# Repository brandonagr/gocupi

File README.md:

Create Thick TSP
================
forked the code in order to draw thicker lines to get more contrast. For detailed descriptions see file createThickTSP
How to set start point and pinup see http://4um.gocupi.com/t/draw-tsp-with-different-line-thickness/61

gocupi
======

Polargraph (vertical plotter / drawing machine) written in Go. Inspired by [Polargraph](http://www.polargraph.co.uk/) and [drawbot](http://marginallyclever.com/blog/drawbot/) projects, designed with the help of the [Dallas Makerspace](http://dallasmakerspace.org/)

Gocupi is different from existing systems in that it uses a Raspberry Pi to do most of the processing instead of relying on a microcontroller to parse commands. This gives it the ability to render complex svg files and patterns that would not fit in memory on a microcontroller.

**A kit with all the hardware needed is now [available at gocupi.com](http://www.gocupi.com/store/)**

Check out the [project page](http://brandonagr.github.io/gocupi/) for a general description, there are also several [wiki pages](https://github.com/brandonagr/gocupi/wiki) with additional information as well as a [forum](http://4um.gocupi.com).

Custom Linux Distro
===================

You can now [download](https://www.dropbox.com/s/6l89m04kcqiwlgb/gocupi_boot_image.zip?dl=0) a custom linux distrobution built from Raspbian with all gocupi software pre-installed.
Unzip the download and copy files to blank SD card (do not build the image). Put the card in the Pi and Bob's your uncle.

If you choose the method above (custom linux distro) then you can skip to the bottom of this document to section "Run gocupi".

Manual Installation Quickstart Guide
================

(Start with something well supported i.e. Raspbian Wheezy.) 

Install Go
-----------
The full install guide is on [golang.org](http://golang.org/doc/install). For the Raspberry Pi you can [download precompiled binaries](http://dave.cheney.net/unofficial-arm-tarballs) to avoid the lengthy process of building go from source.

For example, installing go to the default location with a precompiled binary on a raspberry pi just takes 3 commands:

    wget http://dave.cheney.net/paste/go.1.3.linux-arm~multiarch-armv6-1.tar.gz
    sudo tar -C /usr/local -xzf go.1.3.linux-arm~multiarch-armv6-1.tar.gz
    sudo echo 'export PATH=$PATH:/usr/local/go/bin' >> ~/.profile

(You must set GOROOT also if you install go to someplace besides the default /usr/local/go)

Fix the serial communication (for Raspberry Pi)
----------------------------
Change the default serial communication by editing /boot/cmdline.txt and remove references to `/dev/ttyAMA0`

Disable the getty on that serial port in /etc/inittab by commenting out references to `/dev/ttyAMA0`

In order to reset the serial communication port we need to `sudo reboot`

Setup gopath folder
----------------------------
Setup the folder for your gopath and set some path variables

    mkdir ~/gopath
    sudo echo 'export GOPATH=$HOME/gopath' >> ~/.profile
    sudo echo 'export PATH=$PATH:$HOME/gopath/bin' >> ~/.profile

Install needed dependency
---------------------
Update apt-get, install mercurial, and reboot

    sudo apt-get update
    sudo apt-get install mercurial
    sudo reboot

Download and build gocupi
---------------------------
From your home directory

    go get github.com/brandonagr/gocupi

Run gocupi
----------
`gocupi` The gocupi executable should now be in your $GOPATH\bin folder, you can run the command with no arguments to display the help and what command are available

`gocupi setup 1000 700 700` The setup command can be used to initialize the dimensions of the polargraph hardware, the setup is stored in the generated gocupi_config.xml file

`gocupi -toimage grid 100 10` The -toimage flag causes the system to draw to an output.png instead of trying to control the stepper motors over serial

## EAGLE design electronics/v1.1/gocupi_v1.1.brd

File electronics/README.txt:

Designs are a work in progress, issues may be submitted through the repository at https://github.com/brandonagr/gocupi or emailed directly to Brandon Dunson 'dunson at gocupi dot com'

gocupi hardware by Brandon Dunson is licensed under a Creative Commons Attribution-SharAlike 4.0 International License.

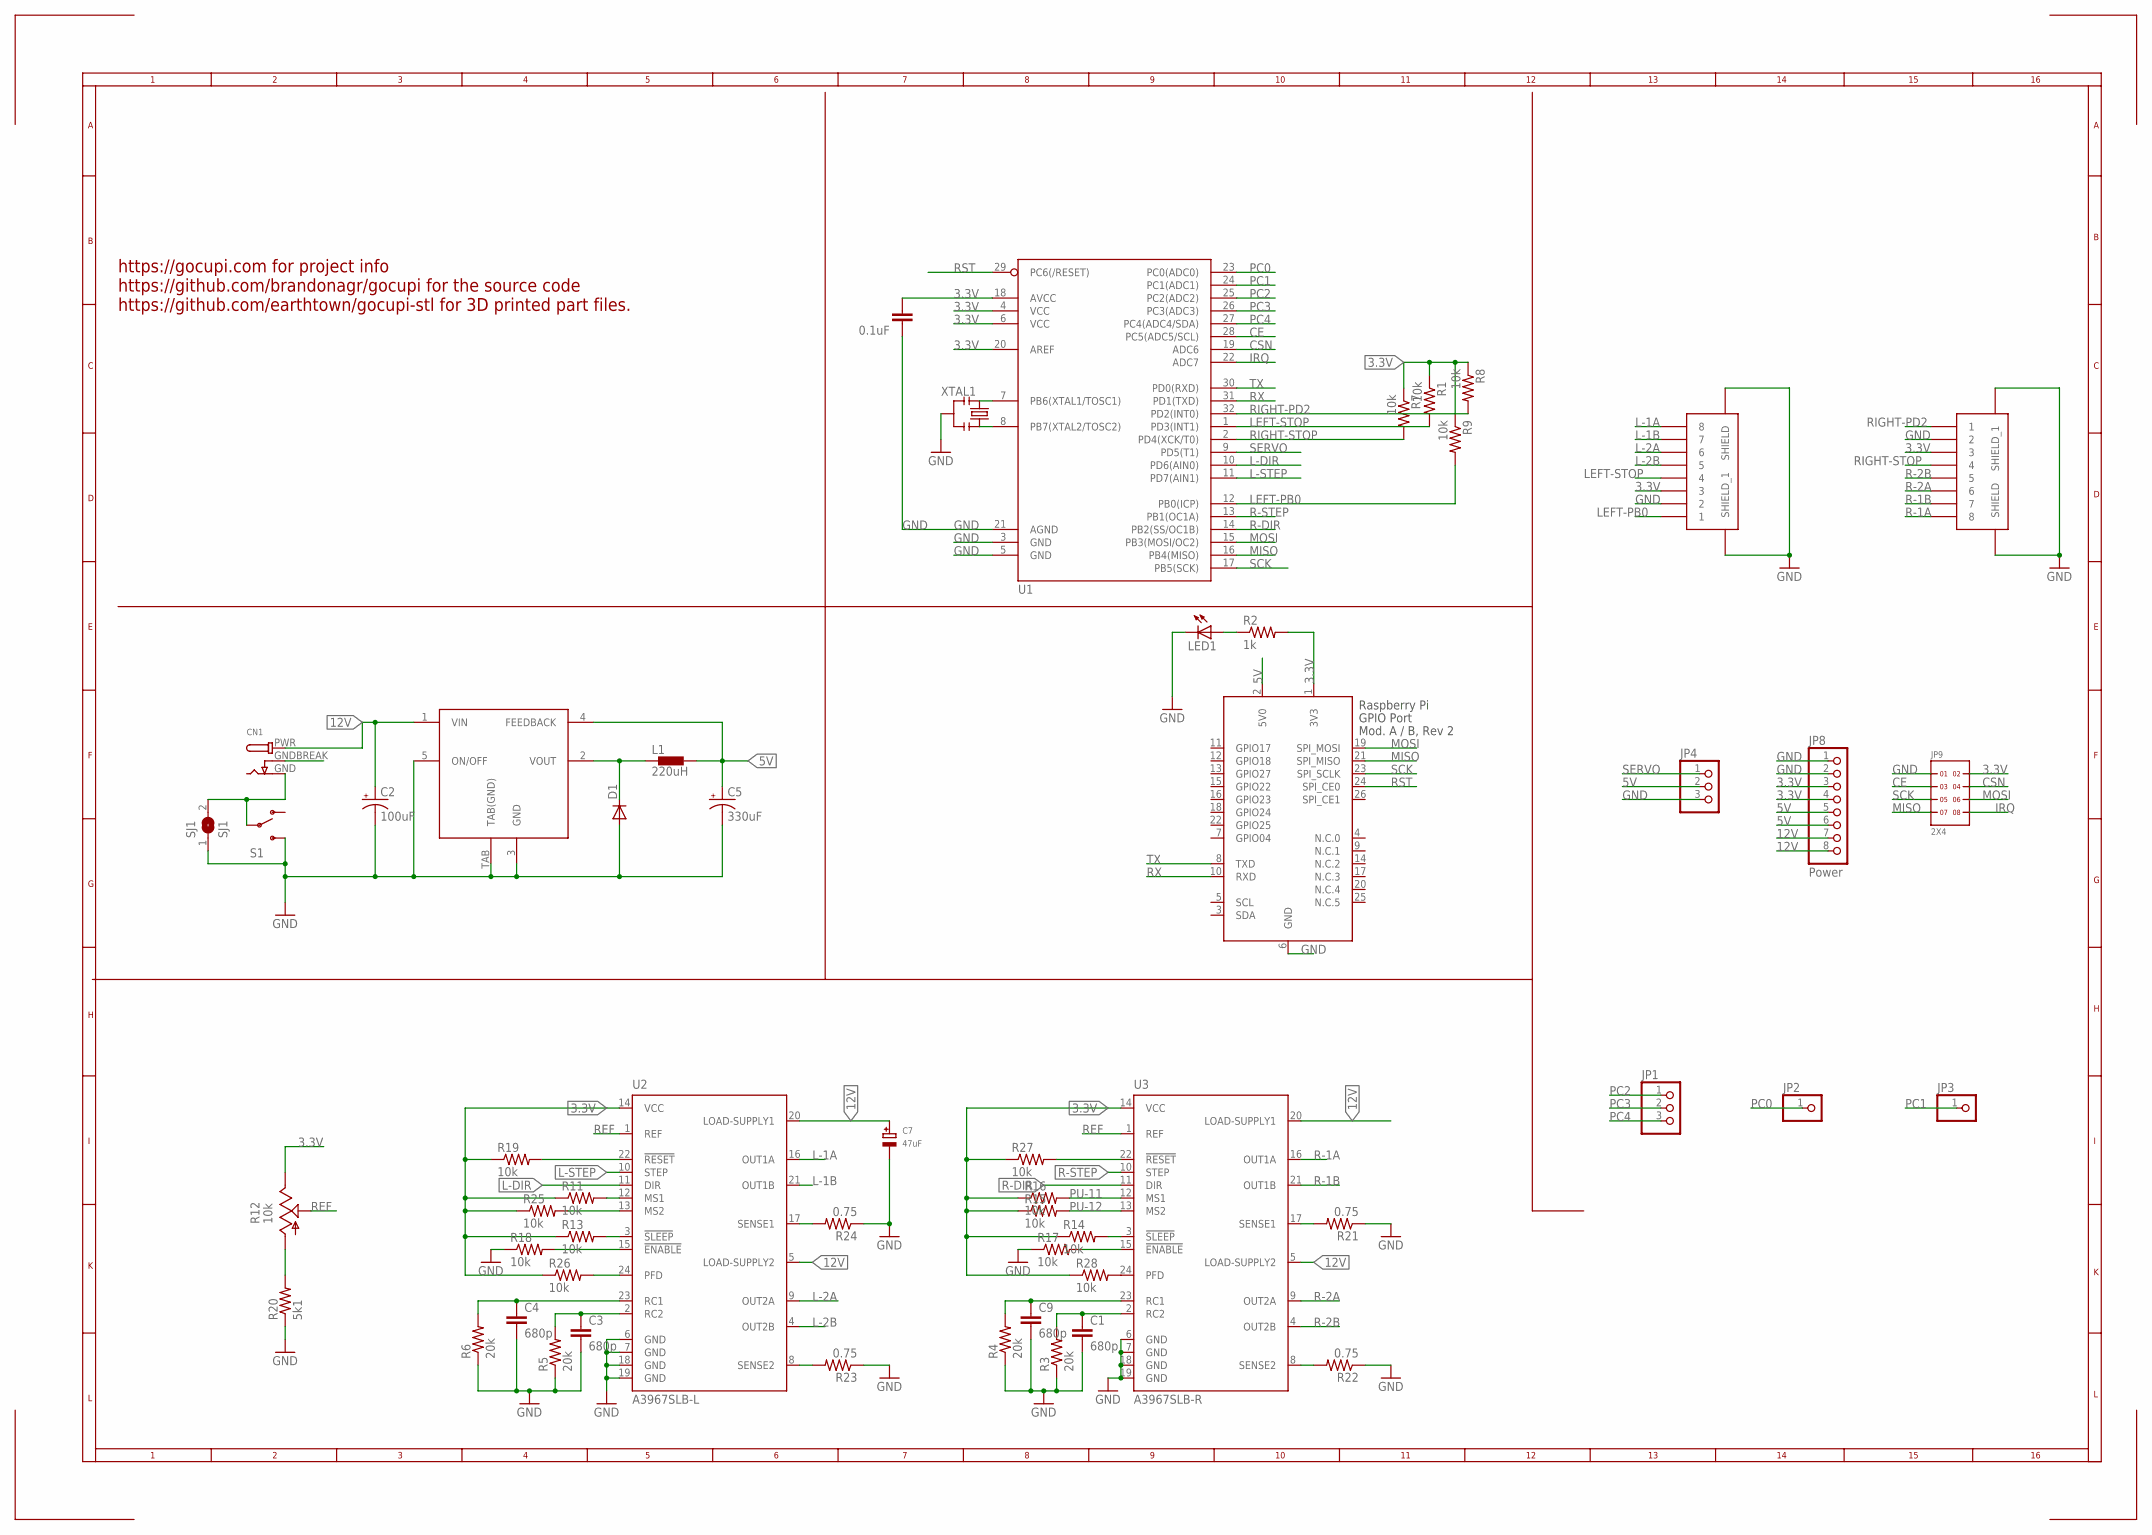
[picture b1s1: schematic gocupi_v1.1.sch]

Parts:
C1, C3, C4, C9: 680p; 0805
C2: 100uF; PANASONIC_D
C5: 330uF; PANASONIC_F
C7: 47uF; PANASONIC_C
C8: 0.1uF; 0805
CN1: DCBARRELSMT_CORRECT; DCJACK_2MM_SMT
D1: DIODE-SOD-123; SOD-123
JP1: PINHD-1X3CB; 1X03-CLEANBIG
JP2, JP3: PINHD-1X1CB; 1X01-CLEANBIG
JP4: PINHD-1X3; 1X03
JP8: Power; 1X08-CLEANBIG
JP9: 2X4
L1: 220uH; SDR1305
LED1: LEDCHIPLED_0805; CHIPLED_0805
R1, R7, R8, R9, R11, R13, R14, R15, R16, R17, R18, R19, R25, R26, R27, R28: 10k; 0805
R2: 1k; 0805
R3, R4, R5, R6: 20k; 0805
R12: 10k; SM-42/43A
R20: 5k1; 0805
R21, R22, R23, R24: 0.75; 0805
RJ45-L, RJ45-R: RJ45_SMD
S1: SWITCH-SPST-SMD-A
SJ1: SJ1; SJ
U1: ATMEGA328_SMT; TQFP32-08
U2: A3967SLB-L; SO24W
U3: A3967SLB-R; SO24W
U4: TL2575; TO263_5
X1: RASPI_BOARD_AB_E2P; RASPI_BOARD_AB_EDGES_2DRILL_PAD
XTAL1: 10MHz; RESONATOR-SMD

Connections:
3.3V: C8.1, JP8.3, JP8.4, JP9.2, R1.1, R2.2, R7.1, R8.1, R9.1, R11.1, R12.3 (E), R13.1, R14.1, R15.1, R16.1, R19.1, R25.1, R26.1, R27.1, R28.1, RJ45-L.P$3 (3), RJ45-R.P$3 (3), U1.4 (VCC), U1.6 (VCC), U1.18 (AVCC), U1.20 (AREF), U2.14 (VCC), U3.14 (VCC), X1.1 (3V3)
5V: C5.+, JP4.2, JP8.5, JP8.6, L1.P$2 (2), U4.4 (FEEDBACK), X1.2 (5V0)
12V: C2.+, C7.+, CN1.PWR, JP8.7, JP8.8, U2.5 (LOAD-SUPPLY2), U2.20 (LOAD-SUPPLY1), U3.5 (LOAD-SUPPLY2), U3.20 (LOAD-SUPPLY1), U4.1 (VIN)
B-GND: CN1.GNDBREAK
CE: JP9.3, U1.28 (PC5(ADC5/SCL))
CSN: JP9.4, U1.19 (ADC6)
GND: C1.2, C2.-, C3.2, C4.2, C5.-, C7.-, C8.2, C9.2, D1.A, JP4.3, JP8.1, JP8.2, JP9.1, LED1.C, R3.1, R4.1, R5.1, R6.1, R17.1, R18.1, R20.1, R21.1, R22.1, R23.1, R24.1, RJ45-L.P$2 (2), RJ45-L.P$SHIELD (SHIELD), RJ45-L.P$SHIELD_1 (SHIELD_1), RJ45-R.P$2 (2), RJ45-R.P$SHIELD (SHIELD), RJ45-R.P$SHIELD_1 (SHIELD_1), S1.3 (S), SJ1.1, U1.3 (GND), U1.5 (GND), U1.21 (AGND), U2.6 (GND), U2.7 (GND), U2.18 (GND), U2.19 (GND), U3.6 (GND), U3.7 (GND), U3.18 (GND), U3.19 (GND), U4.3 (GND), U4.5 (ON/OFF), U4.TAB (TAB(GND)), X1.6 (GND), XTAL1.2
IRQ: JP9.8, U1.22 (ADC7)
L-1A: RJ45-L.P$8 (8), U2.16 (OUT1A)
L-1B: RJ45-L.P$7 (7), U2.21 (OUT1B)
L-2A: RJ45-L.P$6 (6), U2.9 (OUT2A)
L-2B: RJ45-L.P$5 (5), U2.4 (OUT2B)
L-DIR: U1.10 (PD6(AIN0)), U2.11 (DIR)
L-STEP: U1.11 (PD7(AIN1)), U2.10 (STEP)
LEFT-PB0: R9.2, RJ45-L.P$1 (1), U1.12 (PB0(ICP))
LEFT-STOP: R1.2, RJ45-L.P$4 (4), U1.1 (PD3(INT1))
MISO: JP9.7, U1.16 (PB4(MISO)), X1.21 (SPI_MISO)
MOSI: JP9.6, U1.15 (PB3(MOSI/OC2)), X1.19 (SPI_MOSI)
unnamed: D1.C, L1.P$1 (1), U4.2 (VOUT)
unnamed: CN1.GND, S1.2, SJ1.2
unnamed: LED1.A, R2.1
unnamed: R28.2, U3.24 (PFD)
unnamed: R19.2, U2.22 (!RESET)
unnamed: R11.2, U2.12 (MS1)
unnamed: R26.2, U2.24 (PFD)
unnamed: R27.2, U3.22 (!RESET)
unnamed: R25.2, U2.13 (MS2)
unnamed: R17.2, U3.15 (!ENABLE)
unnamed: R14.2, U3.3 (!SLEEP)
unnamed: R13.2, U2.3 (!SLEEP)
unnamed: R12.1 (A), R20.2
unnamed: R18.2, U2.15 (!ENABLE)
unnamed: C4.1, R6.2, U2.23 (RC1)
unnamed: C3.1, R5.2, U2.2 (RC2)
unnamed: R24.2, U2.17 (SENSE1)
unnamed: R21.2, U3.17 (SENSE1)
unnamed: R23.2, U2.8 (SENSE2)
unnamed: C9.1, R4.2, U3.23 (RC1)
unnamed: R22.2, U3.8 (SENSE2)
unnamed: C1.1, R3.2, U3.2 (RC2)
unnamed: U1.7 (PB6(XTAL1/TOSC1)), XTAL1.1
unnamed: U1.8 (PB7(XTAL2/TOSC2)), XTAL1.3
PC0: JP2.1, U1.23 (PC0(ADC0))
PC1: JP3.1, U1.24 (PC1(ADC1))
PC2: JP1.1, U1.25 (PC2(ADC2))
PC3: JP1.2, U1.26 (PC3(ADC3))
PC4: JP1.3, U1.27 (PC4(ADC4/SDA))
PU-11: R16.2, U3.12 (MS1)
PU-12: R15.2, U3.13 (MS2)
R-1A: RJ45-R.P$8 (8), U3.16 (OUT1A)
R-1B: RJ45-R.P$7 (7), U3.21 (OUT1B)
R-2A: RJ45-R.P$6 (6), U3.9 (OUT2A)
R-2B: RJ45-R.P$5 (5), U3.4 (OUT2B)
R-DIR: U1.14 (PB2(SS/OC1B)), U3.11 (DIR)
R-STEP: U1.13 (PB1(OC1A)), U3.10 (STEP)
REF: R12.2 (S), U2.1 (REF), U3.1 (REF)
RIGHT-PD2: R8.2, RJ45-R.P$1 (1), U1.32 (PD2(INT0))
RIGHT-STOP: R7.2, RJ45-R.P$4 (4), U1.2 (PD4(XCK/T0))
RST: U1.29 (PC6(/RESET)), X1.24 (SPI_CE0)
RX: U1.31 (PD1(TXD)), X1.10 (RXD)
SCK: JP9.5, U1.17 (PB5(SCK)), X1.23 (SPI_SCLK)
SERVO: JP4.1, U1.9 (PD5(T1))
TX: U1.30 (PD0(RXD)), X1.8 (TXD)

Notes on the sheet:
https://gocupi.com for project info https://github.com/brandonagr/gocupi for the source code https://github.com/earthtown/gocupi-stl for 3D printed part files.

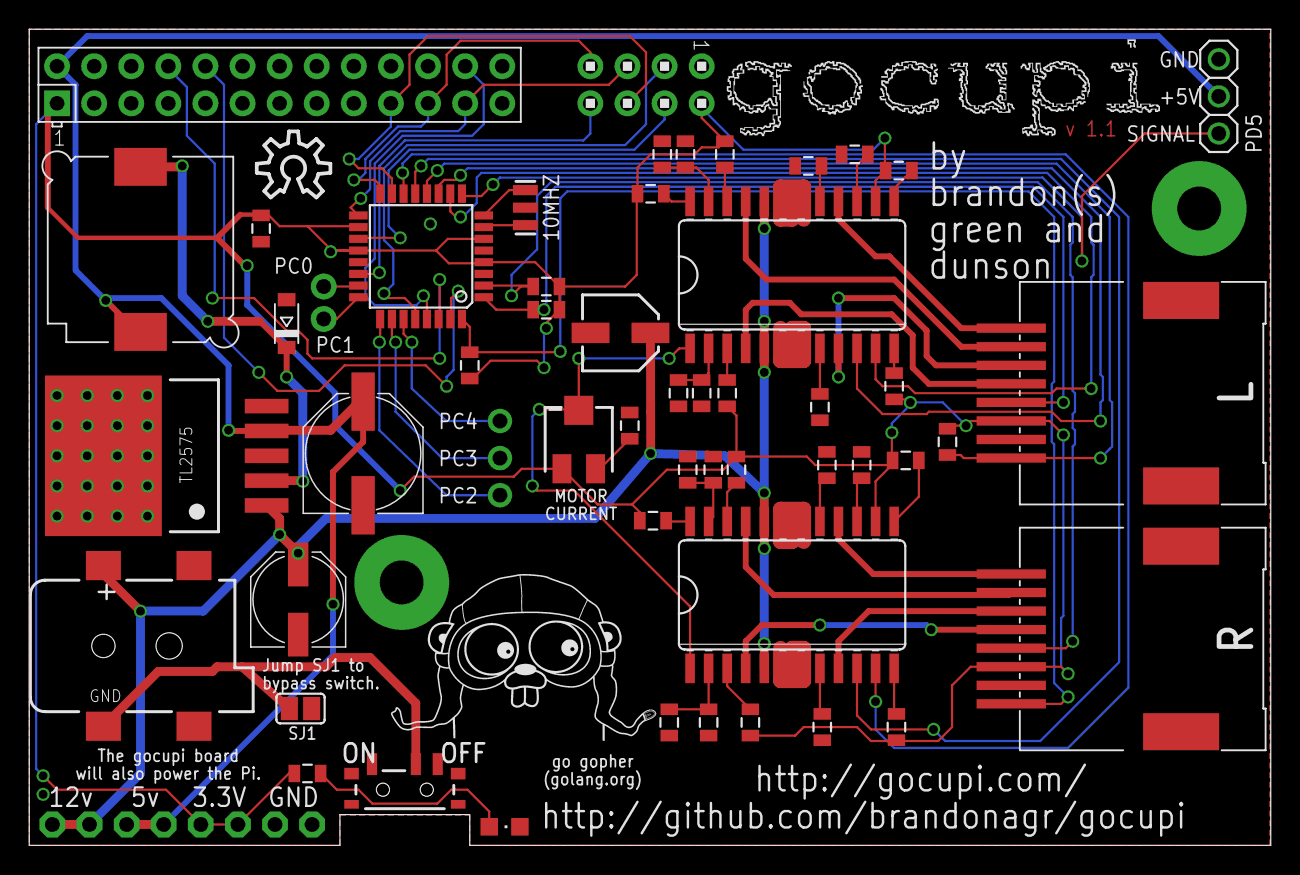
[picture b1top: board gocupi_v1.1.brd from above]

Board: 4 copper layers, 85.0 x 55.9 mm, 59 parts (1 on the bottom side), 62 nets.

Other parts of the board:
U$1: OSHWLOGO_TOP_0.2
U$2: LETTERS
U$3: GO_BLACK
U$5: PI_BLACK

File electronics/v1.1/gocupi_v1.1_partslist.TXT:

Partlist

Exported from gocupi_v1.1.brd at 9/12/2016 5:10:11 PM

EAGLE Version 6.4.0 Copyright (c) 1988-2013 CadSoft

Assembly variant: 

Part     Value              Package                         Library                     Position (mm)         Orientation

C1       680p               0805                            SparkFun-Passives           (46.51375 8.41375)    R270
C2       100uF              PANASONIC_D                     adafruit                    (18.415 16.8275)      R90
C3       680p               0805                            SparkFun-Passives           (44.45 30.95625)      R270
C4       680p               0805                            SparkFun-Passives           (43.33875 47.3075)    R90
C5       330uF              PANASONIC_F                     adafruit                    (22.86 26.82875)      R90
C7       47uF               PANASONIC_C                     microbuilder                (40.48125 35.08375)   R0
C8       0.1uF              0805                            SparkFun-Passives           (15.875 42.2275)      R270
C9       680p               0805                            SparkFun-Passives           (45.085 25.7175)      R90
CN1                         DCJACK_2MM_SMT                  microbuilder                (5.08 13.6525)        R0
D1                          SOD-123                         dp_devices                  (17.62125 35.71875)   R90
JP1                         1X03-CLEANBIG                   adafruit                    (32.22625 26.51125)   R90
JP2                         1X01-CLEANBIG                   adafruit                    (20.16125 38.25875)   R0
JP3                         1X01-CLEANBIG                   adafruit                    (20.16125 36.03625)   R0
JP4                         1X03                            adafruit                    (81.43875 51.27625)   R90
JP8      Power              1X08-CLEANBIG                   adafruit                    (10.4775 1.42875)     R180
JP9      2X4                2X4                             headers(.1in)               (46.0375 53.34)       R180
L1       220uH              SDR1305                         inductors                   (7.62 40.79875)       R0
LED1                        CHIPLED_0805                    adafruit                    (32.54375 1.27)       R270
R1       10k                0805                            SparkFun-Resistors          (35.40125 36.67125)   R180
R2       1k                 0805                            SparkFun-Resistors          (19.05 4.92125)       R180
R3       20k                0805                            SparkFun-Resistors          (43.815 8.41375)      R90
R4       20k                0805                            SparkFun-Resistors          (46.83125 25.7175)    R270
R5       20k                0805                            SparkFun-Resistors          (46.0375 30.95625)    R90
R6       20k                0805                            SparkFun-Resistors          (44.92625 47.3075)    R270
R7       10k                0805                            SparkFun-Resistors          (35.40125 38.25875)   R180
R8       10k                0805                            SparkFun-Resistors          (30.1625 32.86125)    R90
R9       10k                0805                            SparkFun-Resistors          (62.865 27.6225)      R270
R11      10k                0805                            SparkFun-Resistors          (59.21375 31.4325)    R90
R12      10k                SM-42/43A                       pot                         (37.62375 27.78125)   R270
R13      10k                0805                            SparkFun-Resistors          (47.78375 30.95625)   R90
R14      10k                0805                            SparkFun-Resistors          (49.37125 8.41375)    R90
R15      10k                0805                            SparkFun-Resistors          (60.0075 26.3525)     R0
R16      10k                0805                            SparkFun-Resistors          (59.3725 8.09625)     R90
R17      10k                0805                            SparkFun-Resistors          (56.99125 26.035)     R270
R18      10k                0805                            SparkFun-Resistors          (56.515 47.3075)      R0
R19      10k                0805                            SparkFun-Resistors          (47.625 47.3075)      R270
R20      5k1                0805                            SparkFun-Resistors          (41.11625 28.73375)   R270
R21      0.75               0805                            SparkFun-Resistors          (54.61 26.035)        R270
R22      0.75               0805                            SparkFun-Resistors          (54.2925 8.09625)     R90
R23      0.75               0805                            SparkFun-Resistors          (54.13375 30.00375)   R90
R24      0.75               0805                            SparkFun-Resistors          (53.34 46.51375)      R0
R25      10k                0805                            SparkFun-Passives           (59.53125 46.19625)   R0
R26      10k                0805                            SparkFun-Resistors          (42.545 44.60875)     R0
R27      10k                0805                            SparkFun-Resistors          (48.41875 25.7175)    R270
R28      10k                0805                            SparkFun-Resistors          (42.70375 22.225)     R0
RJ45-L   RJ45_SMD           RJ45_SMD                        rj45_smd                    (76.2 30.95625)       R90
RJ45-R   RJ45_SMD           RJ45_SMD                        rj45_smd                    (76.2 14.12875)       R90
S1                          SWITCH-SPST-SMD-A               SwK-SparkFun                (25.7175 3.81)        R180
SJ1      SJ1                SJ                              jumper                      (18.57375 9.36625)    R180
U1                          TQFP32-08                       SparkFun-DigitalIC          (26.82875 40.3225)    R180
U2       A3967SLB-L         SO24W                           allegro                     (52.22875 39.0525)    R0
U3       A3967SLB-R         SO24W                           allegro                     (52.22875 17.145)     R0
U4       TL2575             TO263_5                         TL2575_new                  (8.255 26.67)         R90
X1       RASPI_BOARD_AB_E2P RASPI_BOARD_AB_EDGES_2DRILL_PAD raspberrypi_bastelstube_v13 (0 0)                 R0
XTAL1    10MHz              RESONATOR-SMD                   SwK-SparkFun                (33.9725 43.65625)    R90

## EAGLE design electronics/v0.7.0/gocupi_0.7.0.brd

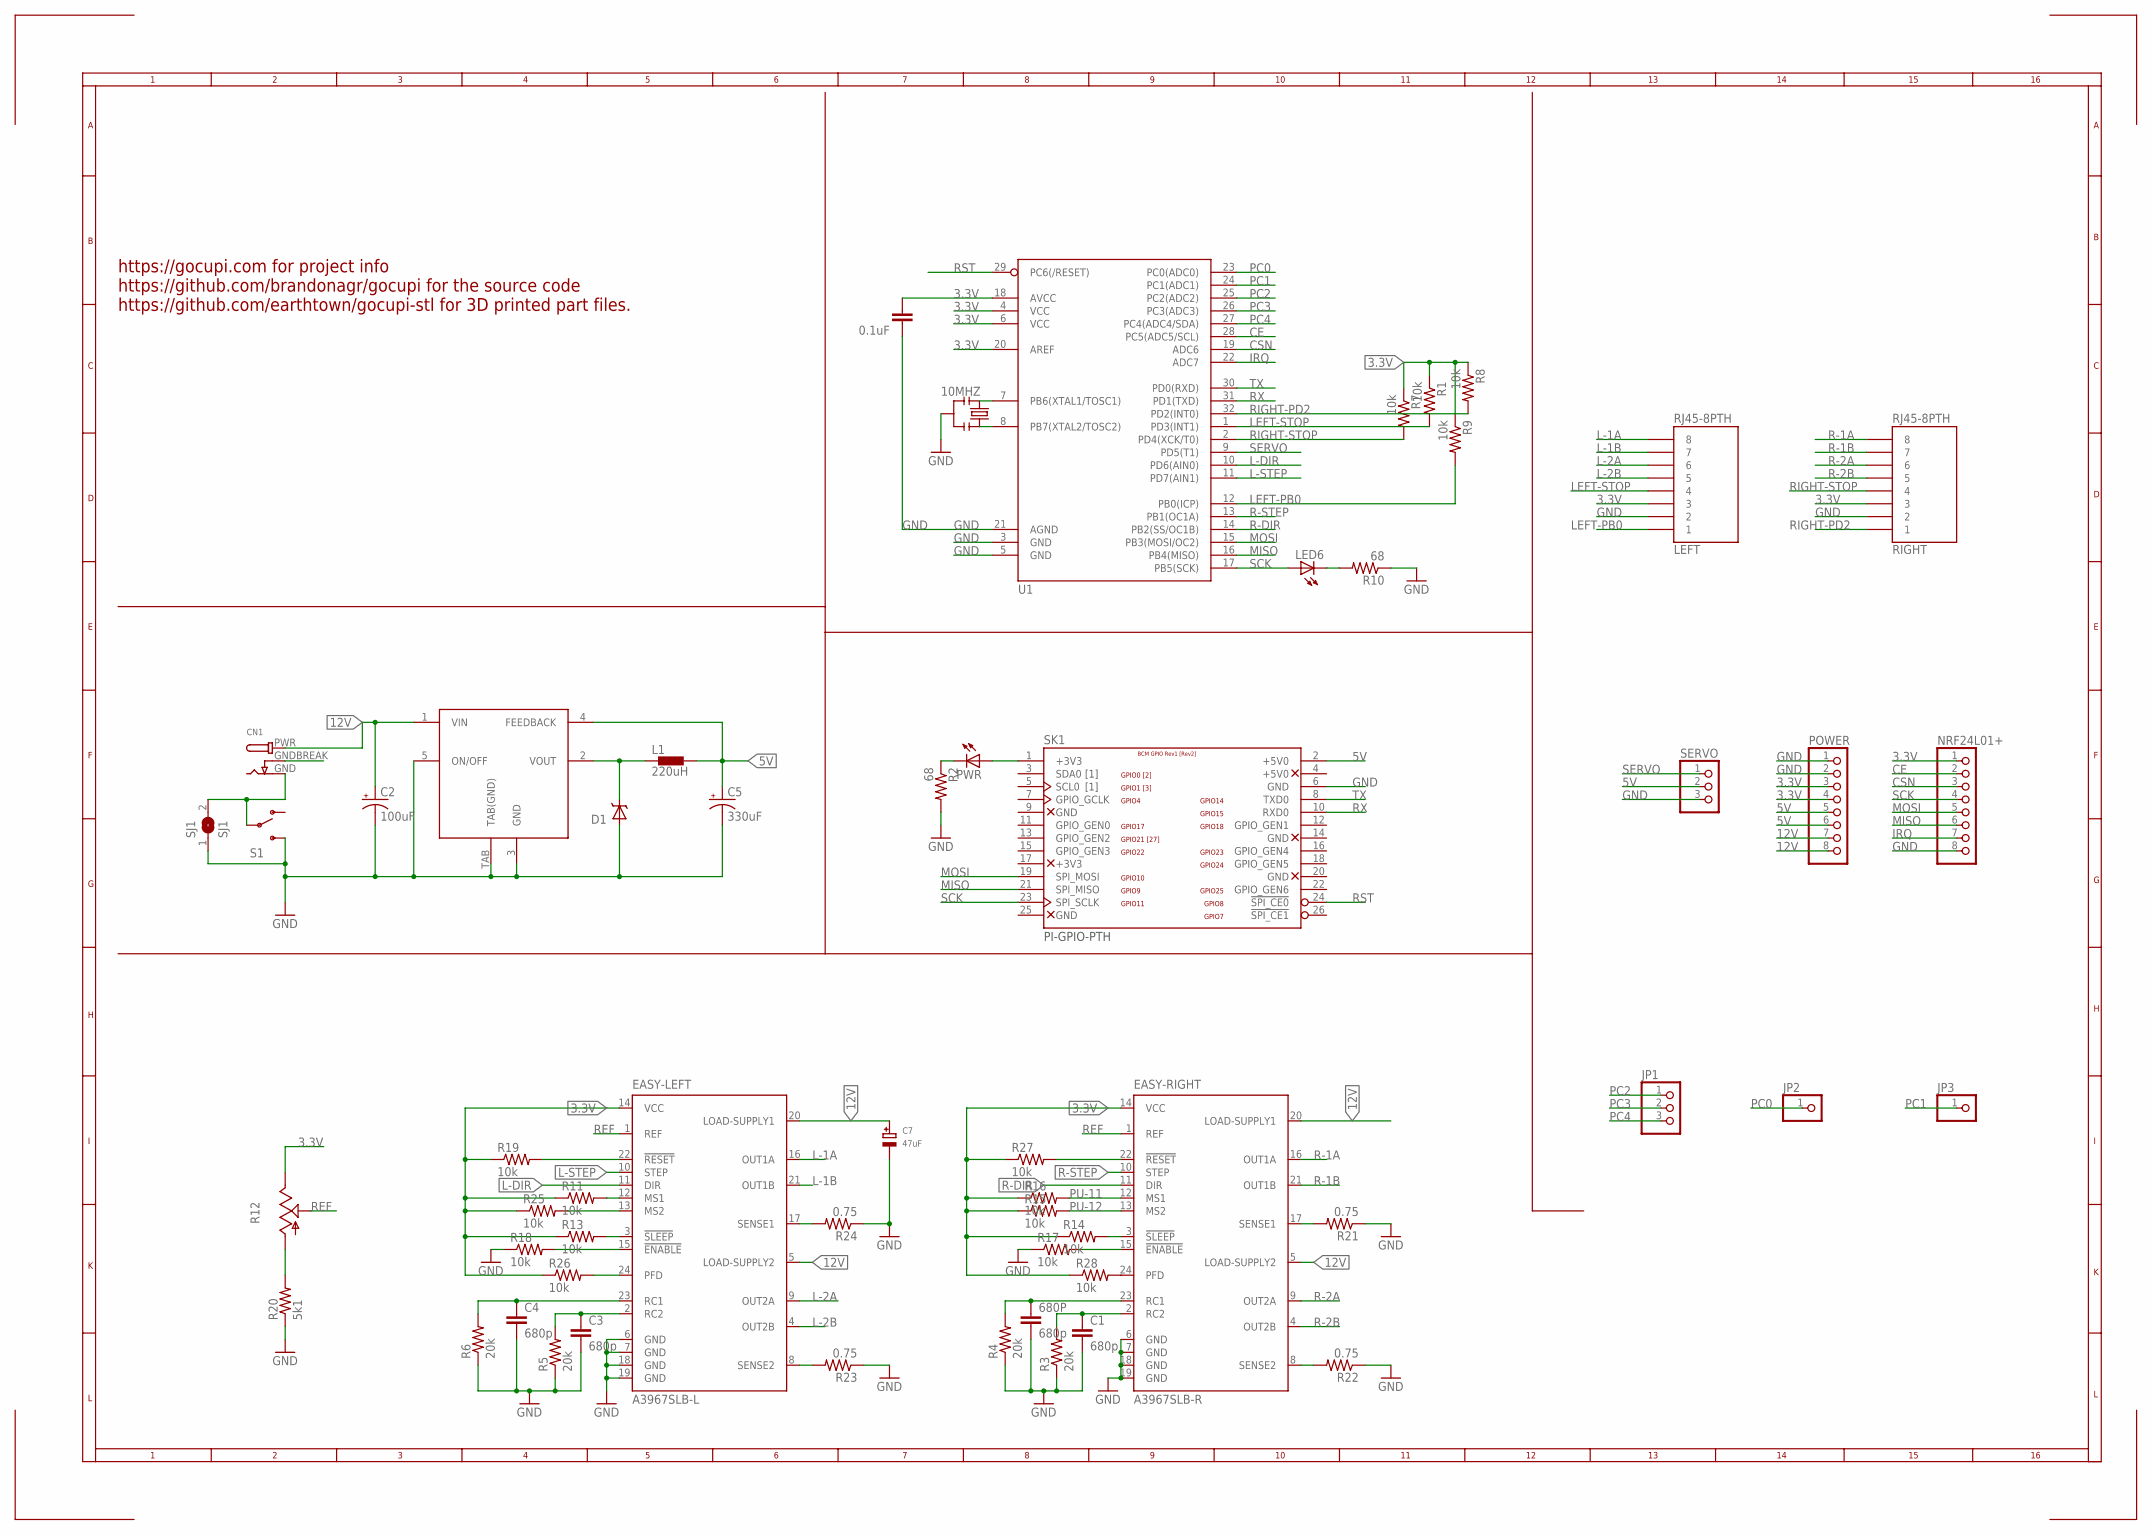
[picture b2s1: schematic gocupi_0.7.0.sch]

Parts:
10MHZ: RESONATORSMD; RESONATOR-SMD
680P: 680p; 0805
C1, C3, C4: 680p; 0805
C2: 100uF; PANASONIC_D
C5: 330uF; PANASONIC_F
C7: 47uF; PANASONIC_C
C8: 0.1uF; 0805
CN1: DCBARRELSMT_CORRECT; DCJACK_2MM_SMT
D1: 1N5819; SMA-DIODE
EASY-LEFT: A3967SLB-L; SO24W
EASY-RIGHT: A3967SLB-R; SO24W
JP1: PINHD-1X3CB; 1X03-CLEANBIG
JP2, JP3: PINHD-1X1CB; 1X01-CLEANBIG
L1: 220uH; SDR1305
LED6: LEDCHIPLED_1206; CHIPLED_1206
LEFT: RJ45-8PTH; RJ45-8
NRF24L01+: PINHD-1X8BIG; 1X08-BIG
POWER: PINHD-1X8CLEANBIG; 1X08-CLEANBIG
PWR: LEDCHIPLED_1206; CHIPLED_1206
R1, R7, R8, R9, R11, R13, R14, R15, R16, R17, R18, R19, R25, R26, R27, R28: 10k; 0805
R2, R10: 68; 0805
R3, R4, R5, R6: 20k; 0805
R12: TRIM_US-SM-42/43A; SM-42/43A
R20: 5k1; 0805
R21, R22, R23, R24: 0.75; 0805
RIGHT: RJ45-8PTH; RJ45-8
S1: SWITCH-SPST-SMD-A
SERVO: PINHD-1X3; 1X03
SJ1: SJ1; SJ
SK1: PI-GPIO-PTH; GPIO-CONNECTOR
U1: ATMEGA328_SMT; TQFP32-08
U$2: TL2575; TO263_5

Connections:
3.3V: C8.1, EASY-LEFT.14 (VCC), EASY-RIGHT.14 (VCC), LEFT.3, NRF24L01+.1, POWER.3, POWER.4, PWR.A, R1.1, R7.1, R8.1, R9.1, R11.1, R12.3 (E), R13.1, R14.1, R15.1, R16.1, R19.1, R25.1, R26.1, R27.1, R28.1, RIGHT.3, SK1.1 (+3V3), U1.4 (VCC), U1.6 (VCC), U1.18 (AVCC), U1.20 (AREF)
5V: C5.+, L1.P$2 (2), POWER.5, POWER.6, SERVO.2, SK1.2 (+5V0), U$2.4 (FEEDBACK)
12V: C2.+, C7.+, CN1.PWR, EASY-LEFT.5 (LOAD-SUPPLY2), EASY-LEFT.20 (LOAD-SUPPLY1), EASY-RIGHT.5 (LOAD-SUPPLY2), EASY-RIGHT.20 (LOAD-SUPPLY1), POWER.7, POWER.8, U$2.1 (VIN)
B-GND: CN1.GNDBREAK
CE: NRF24L01+.2, U1.28 (PC5(ADC5/SCL))
CSN: NRF24L01+.3, U1.19 (ADC6)
GND: 10MHZ.2, 680P.2, C1.2, C2.-, C3.2, C4.2, C5.-, C7.-, C8.2, D1.A, EASY-LEFT.6 (GND), EASY-LEFT.7 (GND), EASY-LEFT.18 (GND), EASY-LEFT.19 (GND), EASY-RIGHT.6 (GND), EASY-RIGHT.7 (GND), EASY-RIGHT.18 (GND), EASY-RIGHT.19 (GND), LEFT.2, NRF24L01+.8, POWER.1, POWER.2, R2.2, R3.1, R4.1, R5.1, R6.1, R10.1, R17.1, R18.1, R20.1, R21.1, R22.1, R23.1, R24.1, RIGHT.2, S1.3 (S), SERVO.3, SJ1.1, SK1.6 (GND), U1.3 (GND), U1.5 (GND), U1.21 (AGND), U$2.3 (GND), U$2.5 (ON/OFF), U$2.TAB (TAB(GND))
IRQ: NRF24L01+.7, U1.22 (ADC7)
L-1A: EASY-LEFT.16 (OUT1A), LEFT.8
L-1B: EASY-LEFT.21 (OUT1B), LEFT.7
L-2A: EASY-LEFT.9 (OUT2A), LEFT.6
L-2B: EASY-LEFT.4 (OUT2B), LEFT.5
L-DIR: EASY-LEFT.11 (DIR), U1.10 (PD6(AIN0))
L-STEP: EASY-LEFT.10 (STEP), U1.11 (PD7(AIN1))
LEFT-PB0: LEFT.1, R9.2, U1.12 (PB0(ICP))
LEFT-STOP: LEFT.4, R1.2, U1.1 (PD3(INT1))
MISO: NRF24L01+.6, SK1.21 (SPI_MISO), U1.16 (PB4(MISO))
MOSI: NRF24L01+.5, SK1.19 (SPI_MOSI), U1.15 (PB3(MOSI/OC2))
unnamed: D1.C, L1.P$1 (1), U$2.2 (VOUT)
unnamed: CN1.GND, S1.2, SJ1.2
unnamed: LED6.C, R10.2
unnamed: PWR.C, R2.1
unnamed: EASY-RIGHT.24 (PFD), R28.2
unnamed: EASY-LEFT.22 (!RESET), R19.2
unnamed: EASY-LEFT.12 (MS1), R11.2
unnamed: EASY-LEFT.24 (PFD), R26.2
unnamed: EASY-RIGHT.22 (!RESET), R27.2
unnamed: EASY-LEFT.13 (MS2), R25.2
unnamed: EASY-RIGHT.15 (!ENABLE), R17.2
unnamed: EASY-RIGHT.3 (!SLEEP), R14.2
unnamed: EASY-LEFT.3 (!SLEEP), R13.2
unnamed: R12.1 (A), R20.2
unnamed: EASY-LEFT.15 (!ENABLE), R18.2
unnamed: C4.1, EASY-LEFT.23 (RC1), R6.2
unnamed: C3.1, EASY-LEFT.2 (RC2), R5.2
unnamed: EASY-LEFT.17 (SENSE1), R24.2
unnamed: EASY-RIGHT.17 (SENSE1), R21.2
unnamed: EASY-LEFT.8 (SENSE2), R23.2
unnamed: 680P.1, EASY-RIGHT.23 (RC1), R4.2
unnamed: EASY-RIGHT.8 (SENSE2), R22.2
unnamed: C1.1, EASY-RIGHT.2 (RC2), R3.2
unnamed: 10MHZ.1, U1.7 (PB6(XTAL1/TOSC1))
unnamed: 10MHZ.3, U1.8 (PB7(XTAL2/TOSC2))
PC0: JP2.1, U1.23 (PC0(ADC0))
PC1: JP3.1, U1.24 (PC1(ADC1))
PC2: JP1.1, U1.25 (PC2(ADC2))
PC3: JP1.2, U1.26 (PC3(ADC3))
PC4: JP1.3, U1.27 (PC4(ADC4/SDA))
PU-11: EASY-RIGHT.12 (MS1), R16.2
PU-12: EASY-RIGHT.13 (MS2), R15.2
R-1A: EASY-RIGHT.16 (OUT1A), RIGHT.8
R-1B: EASY-RIGHT.21 (OUT1B), RIGHT.7
R-2A: EASY-RIGHT.9 (OUT2A), RIGHT.6
R-2B: EASY-RIGHT.4 (OUT2B), RIGHT.5
R-DIR: EASY-RIGHT.11 (DIR), U1.14 (PB2(SS/OC1B))
R-STEP: EASY-RIGHT.10 (STEP), U1.13 (PB1(OC1A))
REF: EASY-LEFT.1 (REF), EASY-RIGHT.1 (REF), R12.2 (S)
RIGHT-PD2: R8.2, RIGHT.1, U1.32 (PD2(INT0))
RIGHT-STOP: R7.2, RIGHT.4, U1.2 (PD4(XCK/T0))
RST: SK1.24 (!SPI_CE0), U1.29 (PC6(/RESET))
RX: SK1.10 (RXD0), U1.31 (PD1(TXD))
SCK: LED6.A, NRF24L01+.4, SK1.23 (SPI_SCLK), U1.17 (PB5(SCK))
SERVO: SERVO.1, U1.9 (PD5(T1))
TX: SK1.8 (TXD0), U1.30 (PD0(RXD))

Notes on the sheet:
https://gocupi.com for project info https://github.com/brandonagr/gocupi for the source code https://github.com/earthtown/gocupi-stl for 3D printed part files.

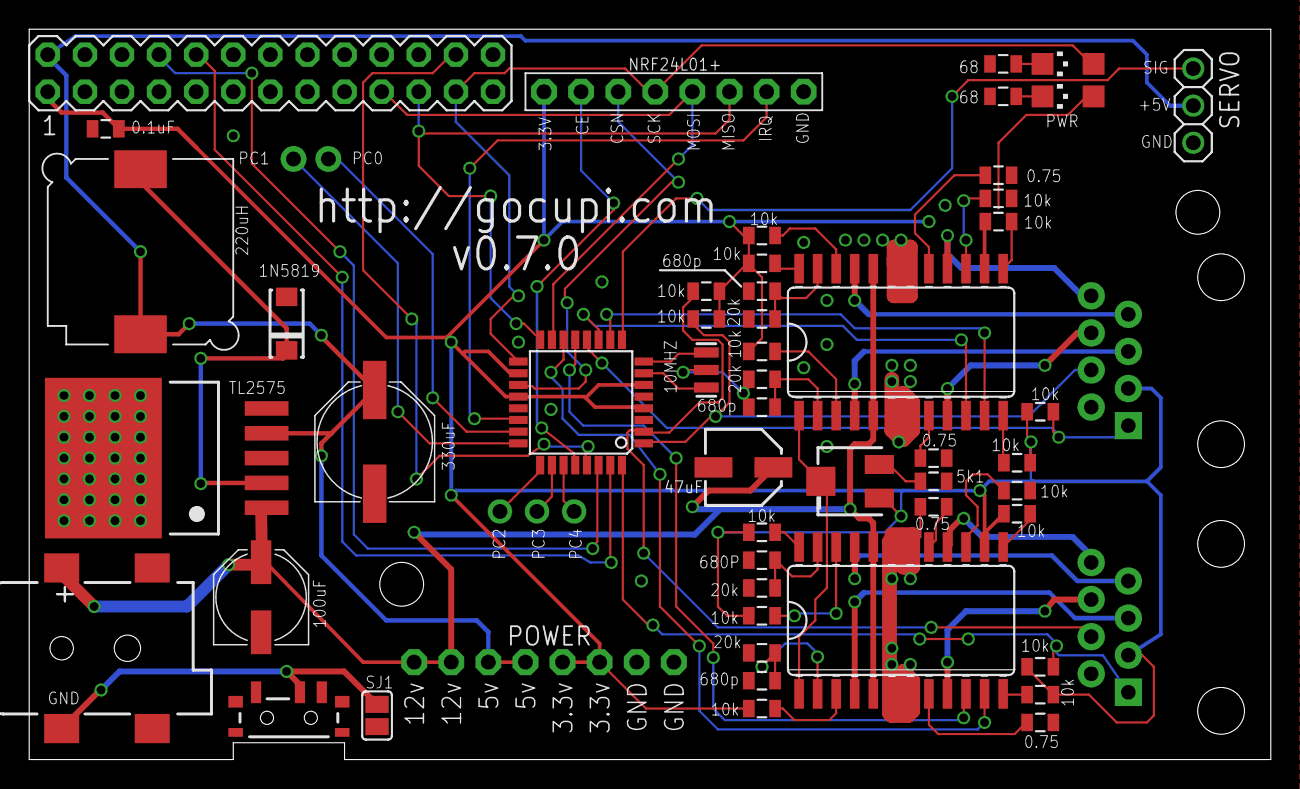
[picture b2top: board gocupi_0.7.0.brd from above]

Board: 4 copper layers, 85.0 x 50.0 mm, 57 parts (0 on the bottom side), 63 nets.

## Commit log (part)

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2012-09-12 Communication with servos over I2C working, next need to create library
2012-10-17 Adding initial plotter code and project code that was previously being synced using Google Drive only
2012-10-18 Begin changing to use channels to generate coordinates to plot
2012-10-18 Create WriteStepsToSerial that will write steps from channel to serial
2012-10-19 Added sliding circle generator and DrawToImage which plots the coordinates to a png for easy previewing
2012-10-19 Add gcode files and very crude support for reading gcode files that only contain straight lines
2012-10-20 Add arduino code, Modify to use 2ms slices and reduce number of printlns in driver
2012-10-20 Add method to log step data to file for analysis
2012-10-21 Add cubic smoothing to a given step generation if there are more than 3 slices
2012-10-21 Add parabolic curve generation, add move back to origin at end of each generation method
2012-10-21 Add scale to gcode path generation
2012-10-21 Change WriteStepsToSerial to assume a data request has already been made, so that it can start communication without having to reset the arduino every time
2012-10-22 Change smoothing to be == 0 instead of using large epsilon
2012-10-22 Add command line interface, Add spirograph generator
2012-10-22 Add PrintUsage for unexpected command
2012-10-23 Add svg support for tsp generated svg files
2012-10-23 Remove extra data files
2012-10-23 Combine two parametric generators into one that takes a function, Add parabolic command that was left out
2012-10-24 Change parabolic generator to generate curves based on polygon
2012-10-24 Refactor common string conversion code in parameter parsing into seperate method
2012-10-26 Begin adding 64x more accurate step generation approach, instead of rounding to integer steps, round to steps * 64
2012-10-29 First pass at conversion to new interpolation based on steps*64 approach
2012-10-29 Got interpolation approach working, switched to 1/8 microsteps instead of 1/4, makes movement smoother and torque seems fine
2012-10-29 Add LinearInterpolator in order to compare against new trapezoid interpolator, clean up code
2012-10-29 Forgot to add interpolater.go
2012-10-30 Change decel policy to change acceleration to get to exit speed instead of just sticking with max accel
2012-10-30 Fix first point not being plotted
2012-10-30 Remove warning on decel calculation
2012-10-30 Improve grid generator to use long lines instead of tracing each cell
2012-10-30 Add sentinel serial value so that steppers can start moving without having to manually push resest button on arduino each time
2012-10-31 Working test file for using /dev/input/event to track mouse
2012-10-31 Fix sentinel auto restarting arduino, an extra 254 value seems to be written to the serial port when it is opened, so changed the arduino code to compare all bytes to sentinel, not just the first byt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
2012-10-31 Add interactive mouse command
2012-11-01 test out using keyboard for movement
2012-11-01 Improve mouse movement to limit number of coords sent per second
2012-11-01 Change mutex to atomic.Load/Store
2012-11-02 Improve mouse tracking, will always be a 1 second lag due to the buffer in the arduino
2012-11-02 Remove /dev/input/event test file
2012-11-06 Add dallas.svg file and slow down acceleration
2012-11-07 Update settings
2012-11-07 Add plotting pos/vel to chart directly instead of having to use excel, removed unnecessary math.Ceil in interpolator that was causing extra error
2012-11-07 Use cosAngle^3 to determine exit speed in order to reduce size of discontinuities in graph of velocity
2012-11-12 Add rendering image by tracing horizontal lines that move up and down based on the grayscale value at any given pixel
2012-11-13 Change horizontal sampling to per mm instead of per pixel, improve look of rendering
2012-11-14 Add example code for how a longer lookahead buffer could be created, would want to create a circular buffer
2012-11-20 Add first part of arc based drawing, added circle line intersection, arc command, next need to displace arc based on sampling an image
2012-11-21 Add image parameter to arc command, add gaussian blur
2012-11-21 Add CoordinateRingBuffer that will be used when implementing more extensive lookahead in interpolater
2012-11-24 Fix -tochart adding extra lines when not needing maxNumberSteps in chart, Add test command to showcase problem with missing lookahead
2013-01-04 Fix arc command sampling outside the image, which resulted in anomylous spikes at some of the edges
2013-01-10 Add raster image and qr code support
2013-03-06 Add const to stepperdriver sketch
2013-03-06 Add mouse setting, update plotinum usage
2013-04-06 Begin adding PathParser to do a better job of parsing svg path commands
2013-04-06 Add simple svg path support, add currently passing svg_tests
2013-04-06 Improve settings names and warnings when drawing goes outside bounds
2013-04-07 Untested arduino support for servo pen up
2013-04-07 Fix PenUpCommand constant to use int instead of hex because Go 1.0.3 thinks it overflows
2013-04-07 Add PenUp coords to test pattern
2013-04-07 Test compiling does not auto save in the arduino ide...
2013-04-07 Fix penup arduino code by not doing the slow transition for now
2013-04-08 Fix svg rendering to not incorrectly move y axis
2013-04-13 Implement ClosePath command
2013-07-15 Add additional Y command to svg box because it seems to be skipping the bottom left
2013-07-15 Fix greater than which needed to be less than, was causing svg top command to start at bottom instead of top...
2013-08-27 Begin adding timeline that generates the time of each step movement, need a better testing approach
2013-08-28 Change settings to use pointer so that it can cheaply be passed around, begin creating test for timeilne
2013-08-28 Fix basic timeline calculation, need to return actual time instead of just percentage of current segment
2013-08-29 Begin creating speedProfile implementation that will manage buffering coordinates and calculating movement speed
2013-08-29 Add the basic linear speed profile
2013-11-22 Fix build error from timeline.go
2013-11-22 Revert "Fix build error from timeline.go"
    This reverts commit b5cb448f1529e6a16643c5dba261b47e59c0cb9a.
2013-11-22 Revert "Add benchmark for circle line collision"
    This reverts commit 9993d4f02a02331e3c475817dd3445f427515879.
2013-11-22 Revert "Begin creating speedProfile implementation that will manage buffering coordinates and calculating movement speed"
    This reverts commit ce28c29edd2026332e76a854f30c19617d78fc06.
2013-11-22 Revert "Begin expanding timeline unit test"
    This reverts commit 9b9548ee3ad465f8136e0a4655fb5d1a615fd8ce.
2013-11-22 Revert "Change settings to use pointer so that it can cheaply be passed around, begin creating test for timeilne"
    This reverts commit 5b004cc6389883bdeeb6da546e36a23d5253956c.
2013-11-22 Revert "Begin adding timeline that generates the time of each step movement, need a better testing approach"
    This reverts commit 912efa34236eee43155305e4f1b5ab952c5a4638.
2014-01-13 Add line command that just bounces a line around the drawing surface for a given starting angle and total distance, potentially useful for seeing how long a pen can possibly draw
2014-06-23 Change help to allow viewing help for a specific command only, instead of always getting a wall of text
2014-06-23 Moving files around to follow proper go project structure
2014-06-23 Allow both passing spool distance on command line or interactive mode
2014-06-23 Fix not handling switch/case correctly for fallthrough case, same cases should be on same line seperated by comma
2014-06-23 Add -flipx and -flipy params that can flip the drawing vertically or horizontally, useful when drawing on the back of a window
2014-07-06 Create PenUpPinUp.svg
    the svg for the all too familiar drawing of Marilyn Monroe (with gocupi watermark in lower left corner)
2014-07-06 gocupi main board files (Eagle and PDF)
2014-07-09 Update CountSteps to include pen transitions so that time estimate is more accurate
2014-07-09 Update README.md
    fix typos
2014-07-10 Added pause on PenUp functionality
2014-07-11 added mercurial
2014-07-11 added some stuff
    serial comm.
    path variables
2014-07-16 Added .gitignore for binary and eclipse project
2014-07-16 Fix: Added new line to end of available commands
2014-07-17 Fill writeData buffer with 0s when about to pauseAfterWrite
2014-07-17 Fixes #3, changed to the typical go approach of returning an error code instead of using panic, which was a bad idea to do when validating user input
2014-07-17 Fixes #2, you still have to put 3 numbers, but you can use 0 as a placeholder to skip updating a particular value, so you can do setup 800 0 0 and it will only change the horizontal distance, or setu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
2014-07-20 Streamline quickstart
2014-07-21 Begin testing using nrf24l01 for wireless gondola
2014-07-25 Create gh-pages branch via GitHub
2014-07-25 Add pictures, improve formatting of main page
2014-07-25 Simplify Readme so it doesn't duplicate page
2014-08-14 No progress on getting wireless nrf24l01+ working w/ gondola board
2014-08-14 Turns out SPI wasn't freezing, its just that the nrf board is always returning data available, even with no server running
2014-08-18 Update gocupi.go
    putting the project in Camelcase forces the sources to be Twice in the Src folder,
    making changes impossible to track... :)
2014-08-19 Gcode Makelangelo Compatible
    Now Gcode has support for MAkelangelo Gcode Generator (Using stock Pen Settings UP = 50), need still to find a way to make it all Gcode compatible
    Gcode has up en down support for using the pretty filters in makelangelo (Spiral for example)
    https://github.com/MarginallyClever/Makelangelo
    (i can give result output of it
2014-08-25 #10 fix flipy help text
2014-12-02 DrawingSurfaceMaxX calculation Fix #12
    Since the origin is the idler pulley and not the DrawingSurfaceMinX, should only subtract MinX once to get MaxX instead of subtracting twice, which gets the width of drawing area but not current MaxX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
2014-12-09 Add SVG center mode, fixes #15
2014-12-09 Update imagearc command to use penup, modification thanks to sergio-daniels, fixes #21
2014-12-12 minor change wording min / max
2014-12-12 removed imagearcNoWhite
2014-12-20 add instruction on how to create a tsp svg with variable circle radius new file: createThickTSP.md
2014-12-20 modified: README.md
2014-12-20 modified: createThickTSP.md
2015-02-26 Update purchase link :)
2015-03-09 meanderStipple
    How to set start point and pinup if using meanderStipple
2015-08-06 Update README.md
    OCD driven format corrections to the documents asthetics.
2015-08-08 Added custom gocupi linux distro
2015-09-11 yet again fixed link to buy a gocupi kit
    is it THAT hard to maintain gocupi.com?
2016-08-06 Hat tip to Dunson for noticing my own github repo was out of sync with my development box. One line of chart.go didn't get the memo...
2016-08-06 Adding configuration property GondolaArmLength_MM Allows a number to be entered which will be added to future (non-zero) L and R measurements entered at setup.
    Changed GetArgsAsFloats to accept more than expectedCount parameters, as
    already indicated by the "Expected at least, only saw" error value so that
    setup can take 3 or more arguments.
    Behavior is backward compatible to all uses prior to existance of the variable,
    and a reminder is printed during the setup call if an existing non-zero
    value for the property exists.
2016-08-06 Removed unintentional extraneous indention from usage message
2016-09-12 Added hardware version 1.1
2016-09-13 Added link to gocupi forum.
2017-12-15 Create LICENSE

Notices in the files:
parts and their libraries:
SparkFun-Passives: Licensing: Creative Commons ShareAlike 4.0 International - https://creativecommons.org/licenses/by-sa/4.0
SparkFun-DigitalIC: Licensing: CC v3.0 Share-Alike You are welcome to use this library for commercial purposes.
